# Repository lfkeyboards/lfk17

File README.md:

# LFK17

Open source 17-key numpad.

License: [CC BY-NC-SA 4.0](https://creativecommons.org/licenses/by-nc-sa/4.0/)

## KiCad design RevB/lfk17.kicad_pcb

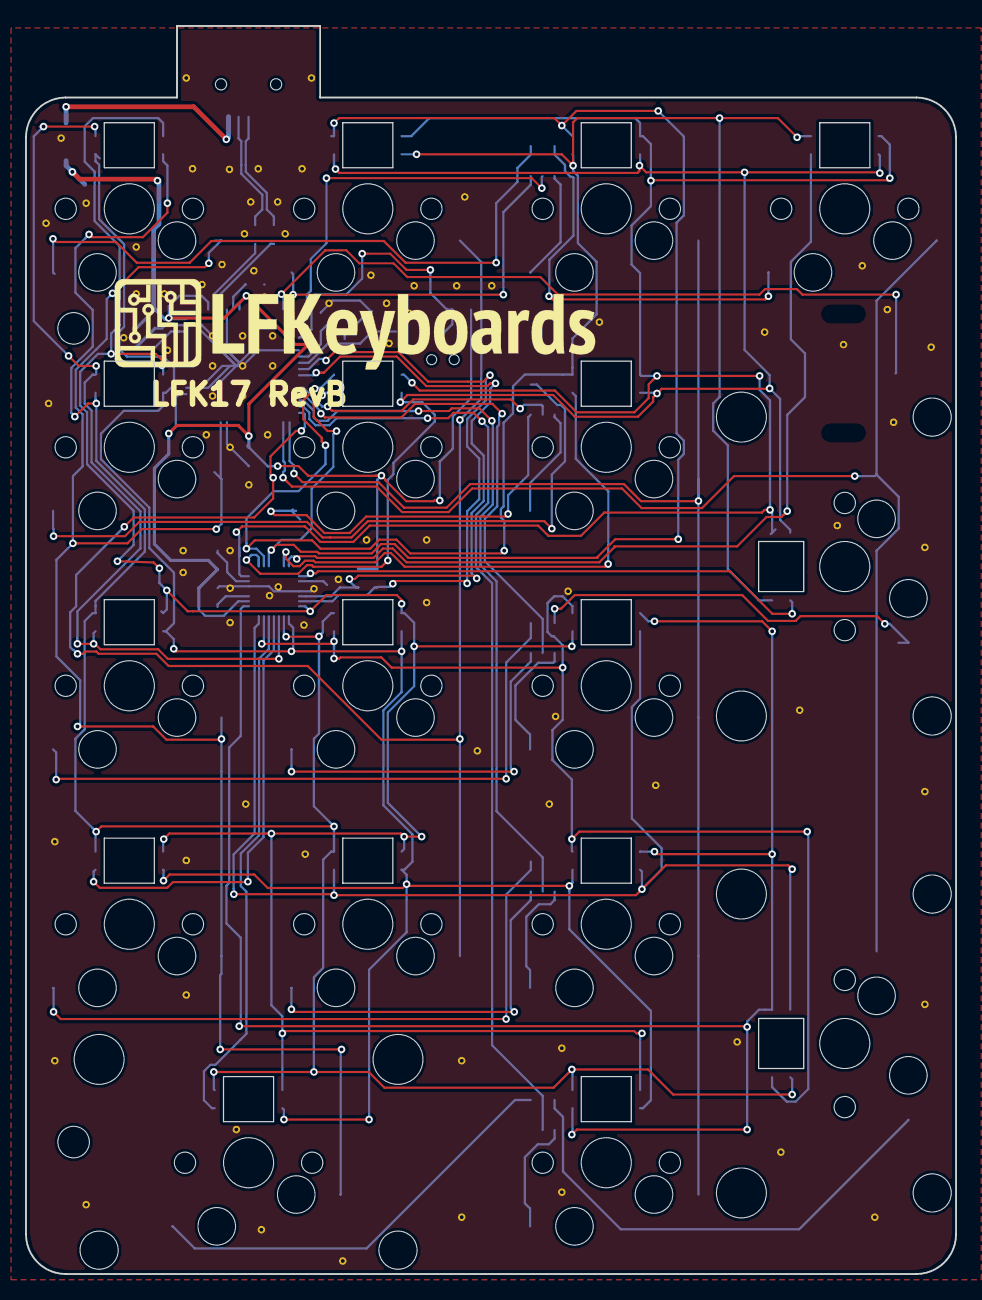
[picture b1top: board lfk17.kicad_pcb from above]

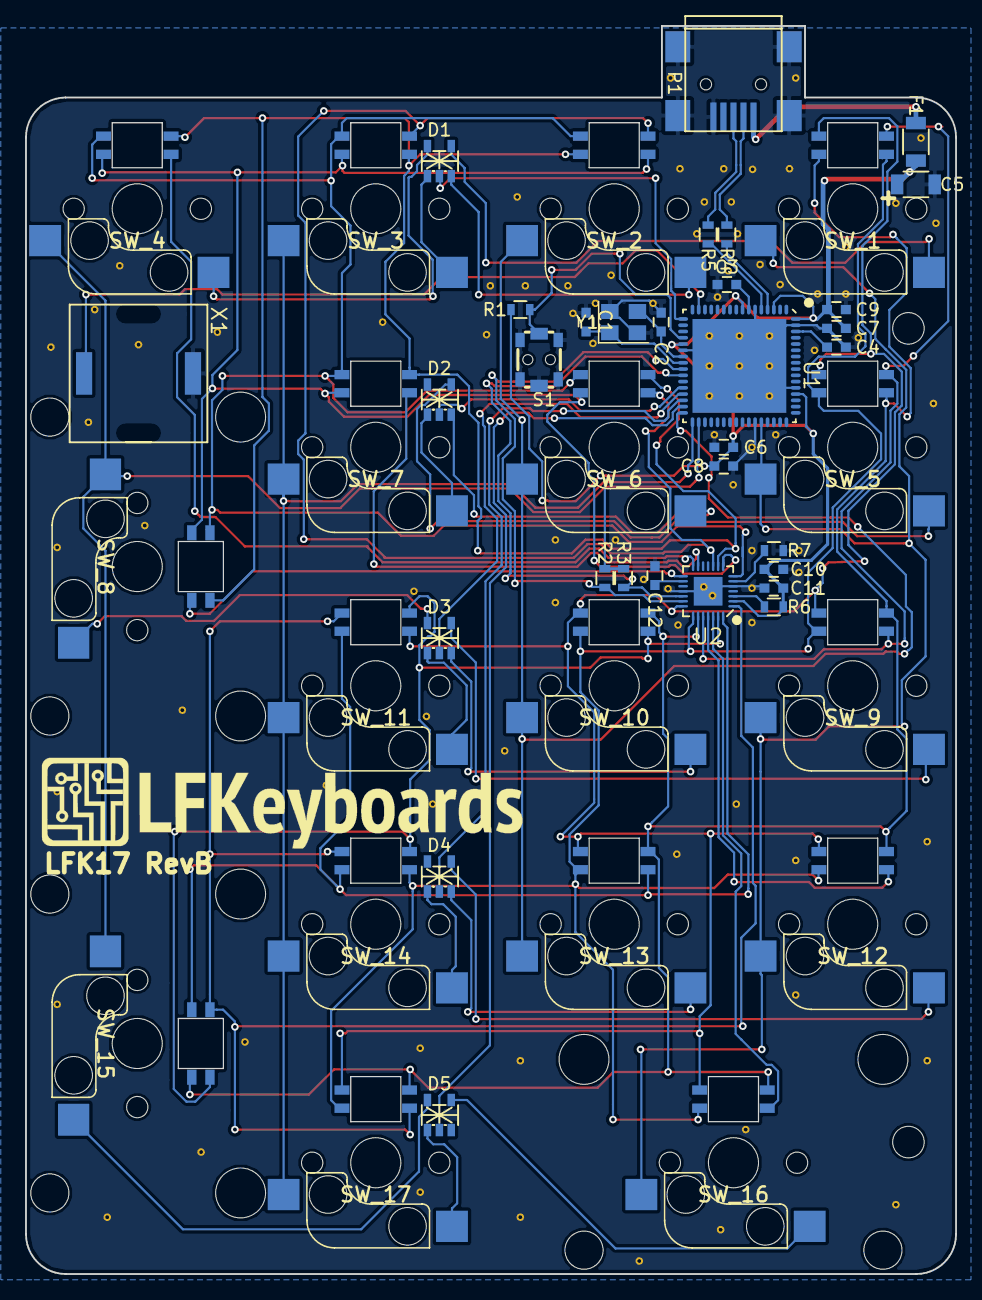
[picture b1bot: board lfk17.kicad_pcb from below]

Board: 2 copper layers, 74.3 x 99.7 mm, 53 parts (27 on the bottom side), 60 nets.

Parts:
C1, C2: 18pF; C_0603
C3, C6, C7, C8, C9, C11, C12: 0.1µF; C_0603
C4, C10: 1µF; C_0603
C5: 4.7µF; C_1206
D1, D2, D3, D4, D5: 1SS309; SC-74A
F1: FP_Small; C_1206
Logo: Logo; LFKeyboards_logo_8mm
Logo#2: Logo; LFKeyboards_logo_8mm
P1: USB_OTG; USB_Mini-B
R1, R6: 10k; R_0603
R2, R3: 4.7k; R_0603
R4, R5: 22; R_0603
R7: 30k; R_0603
S1: SW_PUSH; PTS-820_SPST
STA: Stabilizer; CHERRY_PCB_200_STABILIZER
STA#2, STA#3: Stabilizer; CHERRY_PCB_200_STABILIZER
SW_1, SW_2, SW_3, SW_4, SW_5, SW_6, SW_7, SW_8, SW_9, SW_10, SW_11, SW_12, SW_13, SW_14, SW_15, SW_16, SW_17: MX_LED; MXHS-1U-RGB-ALI-3528-HOLE-NOPAD
U1: AT90USB1286-AU; QFN_64
U2: IS31FL3731; QFN_28
X1: Piezo; piezo-9x9
Y1: CRYSTAL_32x25; Crystal_SMD_3225-4pin_3.2x2.5mm

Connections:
+5v: C5.1, C6.1, C7.1, C8.1, C9.1, C10.1, C11.1, F1.2, R1.1, R2.1, R3.1, R6.1, U1.3, U1.8, U1.21, U1.52, U1.64, U2.2
AUDIO: U1.15, X1.1
Col1: SW_1.MX1, SW_5.MX1, SW_9.MX1, SW_12.MX1, SW_16.MX1, U1.44
Col2: SW_2.MX1, SW_6.MX1, SW_10.MX1, SW_13.MX1, U1.32
Col3: SW_3.MX1, SW_7.MX1, SW_11.MX1, SW_14.MX1, SW_17.MX1, U1.33
Col4: SW_4.MX1, SW_8.MX1, SW_15.MX1, U1.34
D+: R5.1, U1.5
D-: R4.1, U1.4
GND: C1.1, C2.1, C3.2, C4.2, C5.2, C6.2, C7.2, C8.2, C9.2, C10.2, C11.2, C12.1, P1.5, P1.6, R7.1, S1.2, S1.3, U1.6, U1.22, U1.43, U1.53, U1.63, U1.65, U2.5, U2.18, X1.2, Y1.2, Y1.4
L0_1: SW_1.R, SW_5.R, SW_9.R, SW_10.R, SW_11.A, SW_12.R, SW_13.R, SW_16.R, SW_17.R, U2.21
L0_2: SW_1.A, SW_5.G, SW_9.G, SW_10.G, SW_12.G, SW_13.G, SW_14.A, SW_16.G, SW_17.G, U2.22
L0_3: SW_1.G, SW_5.A, SW_9.B, SW_10.B, SW_12.B, SW_13.B, SW_15.A, SW_16.B, SW_17.B, U2.23
L0_4: SW_1.B, SW_5.B, SW_9.A, U2.24
L0_5: SW_12.A, U2.25
L0_6: SW_16.A, U2.26
L0_7: SW_10.A, SW_11.B, SW_14.B, SW_15.B, U2.27
L0_8: SW_11.G, SW_13.A, SW_14.G, SW_15.G, U2.28
L0_9: SW_11.R, SW_14.R, SW_15.R, SW_17.A, U2.1
L1_1: SW_2.R, SW_3.R, SW_4.R, SW_6.R, SW_7.R, SW_8.R, U2.7
L1_2: SW_2.A, SW_3.G, SW_4.G, SW_6.G, SW_7.G, SW_8.G, U2.8
L1_3: SW_2.G, SW_3.A, SW_4.B, SW_6.B, SW_7.B, SW_8.B, U2.9
L1_4: SW_2.B, SW_3.B, SW_6.A, U2.10
L1_7: SW_7.A, U2.13
L1_8: SW_4.A, U2.14
L1_9: SW_8.A, U2.15
LED_SCL: R2.2, U1.25, U2.20
LED_SDA: R3.2, U1.26, U2.19
Matrix-SW_1-D1-4: D1.4, SW_1.MX2
Matrix-SW_2-D1-3: D1.3, SW_2.MX2
Matrix-SW_3-D1-1: D1.1, SW_3.MX2
Matrix-SW_4-D1-5: D1.5, SW_4.MX2
Matrix-SW_5-D2-4: D2.4, SW_5.MX2
Matrix-SW_6-D2-3: D2.3, SW_6.MX2
Matrix-SW_7-D2-1: D2.1, SW_7.MX2
Matrix-SW_8-D3-5: D3.5, SW_8.MX2
Matrix-SW_9-D3-4: D3.4, SW_9.MX2
Matrix-SW_10-D3-3: D3.3, SW_10.MX2
Matrix-SW_11-D3-1: D3.1, SW_11.MX2
Matrix-SW_12-D4-4: D4.4, SW_12.MX2
Matrix-SW_13-D4-3: D4.3, SW_13.MX2
Matrix-SW_14-D4-1: D4.1, SW_14.MX2
Matrix-SW_15-D5-5: D5.5, SW_15.MX2
Matrix-SW_16-D5-4: D5.4, SW_16.MX2
Matrix-SW_17-D5-1: D5.1, SW_17.MX2
unnamed: C1.2, U1.24, Y1.1
unnamed: C2.2, U1.23, Y1.3
unnamed: C3.1, U1.7
unnamed: C4.1, U1.62
unnamed: R6.2, U2.3
unnamed: R7.2, U2.6
unnamed: C12.2, U2.16
RESET: R1.2, S1.1, U1.20
Row1: D1.2, U1.17
Row2: D2.2, U1.28
Row3: D3.2, U1.29
Row4: D4.2, U1.30
Row5: D5.2, U1.31
USB+: P1.3, R5.2
USB-: P1.2, R4.2
VBUS: F1.1, P1.1

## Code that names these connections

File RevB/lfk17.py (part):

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)

matrix_to_mcu = {
    "Row1": "PB7",
    "Row2": "PD3",
    "Row3": "PD4",
    "Row4": "PD5",
    "Row5": "PD6",

    "Col1": "PA7",
    "Col2": "PD7",
    "Col3": "PE0",
    "Col4": "PE1",
}

skidl_lib = SchLib('lfk17_lib_sklib.py', tool=SKIDL)  # Create a SKiDL library object from the new file.
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
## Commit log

2018-01-06 Updated readme, added license
2018-01-06 Add kicad project
2018-01-06 Removed some references to local libs
2018-01-06 Added drill map as dxf
2018-01-16 Added hotswap footprint
